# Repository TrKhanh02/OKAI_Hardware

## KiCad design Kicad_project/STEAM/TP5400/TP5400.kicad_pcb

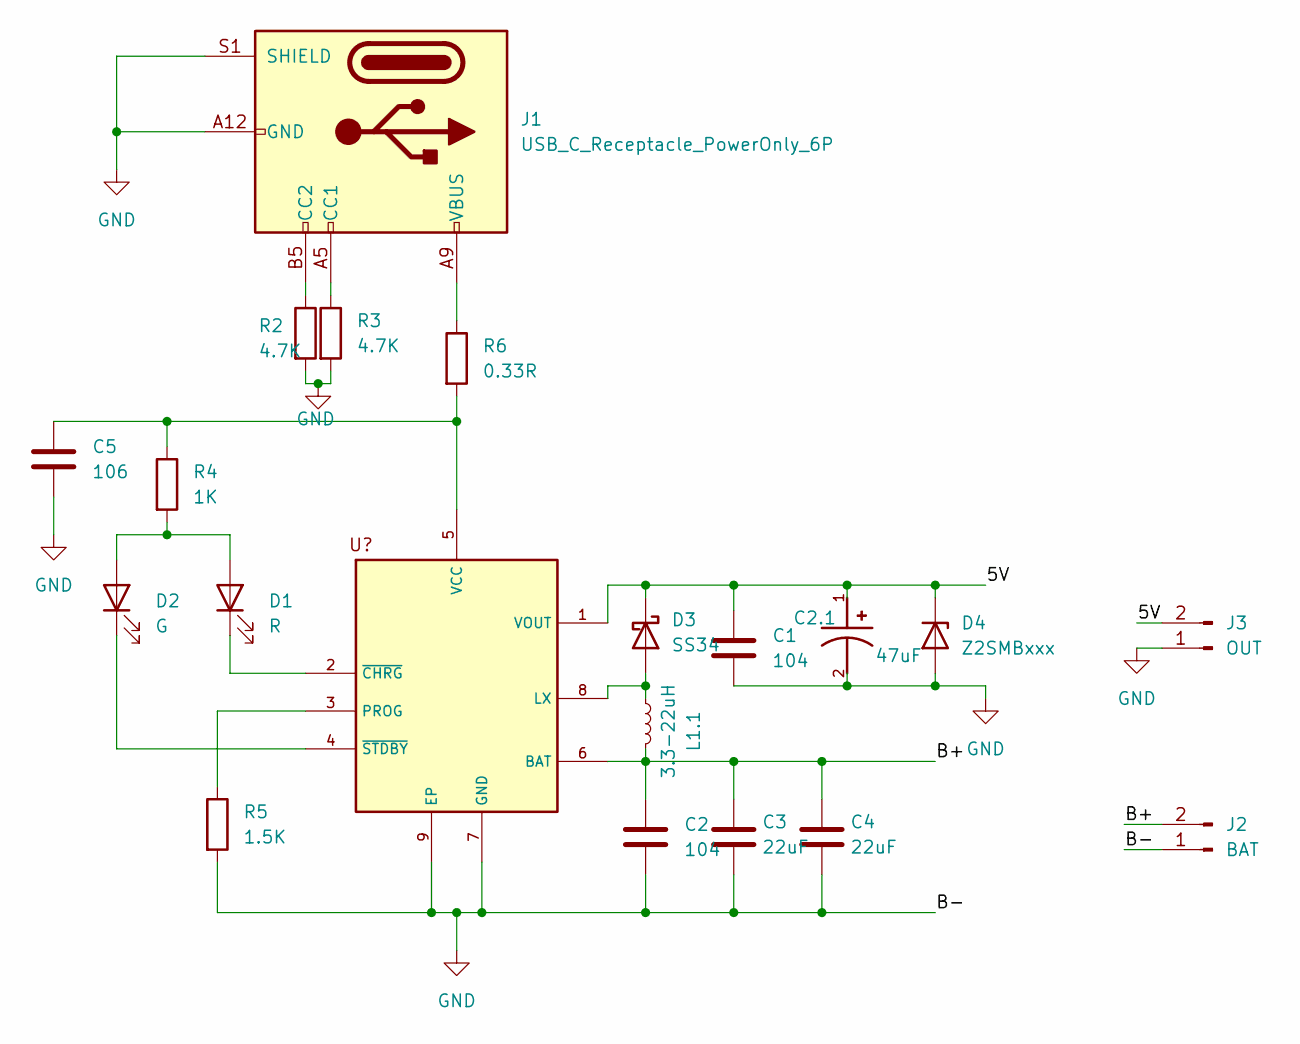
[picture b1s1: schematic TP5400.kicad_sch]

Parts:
C1, C2: 104; C_0805_2012Metric
C2.1: 47uF; CAPMP3216X180N; PARTREV 031320
C3, C4: 22uF; C_1206_3216Metric
C5: 106; C_0805_2012Metric
D1: R; LED_0805_2012Metric
D2: G; LED_0805_2012Metric
D3: SS34; D_SMA
D4: Z2SMBxxx; D_SMB
J1: USB_C_Receptacle_PowerOnly_6P; USB_C_Receptacle_GCT_USB4125-xx-x-0190_6P_TopMnt_Horizontal
J2: BAT; PinSocket_1x02_P2.54mm_Vertical
J3: OUT; PinSocket_1x02_P2.54mm_Vertical
L1.1: 3.3-22uH; L_Ferrocore_DLG-0705
R2, R3: 4.7K; R_0805_2012Metric_Pad1.20x1.40mm_HandSolder
R4: 1K; R_0805_2012Metric_Pad1.20x1.40mm_HandSolder
R5: 1.5K; R_0805_2012Metric_Pad1.20x1.40mm_HandSolder
R6: 0.33R; R_2512_6332Metric
U1: TP5400

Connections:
/5V: C1.1, C2.1.1, D3.1 (K), D4.1 (K), J3.2, U1.1 (VOUT)
/B+: C2.1, C3.1, C4.1, J2.2, L1.1.1, U1.6 (BAT)
GND: C1.2, C2.2, C2.1.2, C3.2, C4.2, C5.2, D4.2 (A), J1.A12 (GND), J1.B12 (GND), J1.S1 (SHIELD), J2.1, J3.1, R2.2, R3.2, R5.2, U1.7 (GND), U1.9 (EP)
unnamed: D1.2 (A), D2.2 (A), R4.2
unnamed: D1.1 (K), U1.2 (~CHRG)
unnamed: D2.1 (K), U1.4 (~STDBY)
unnamed: D3.2 (A), L1.1.2, U1.8 (LX)
unnamed: J1.A5 (CC1), R3.1
unnamed: J1.B5 (CC2), R2.1
unnamed: J1.A9 (VBUS), J1.B9 (VBUS), R6.1
unnamed: R5.1, U1.3 (PROG)
unnamed: C5.1, R4.1, R6.2, U1.5 (VCC)

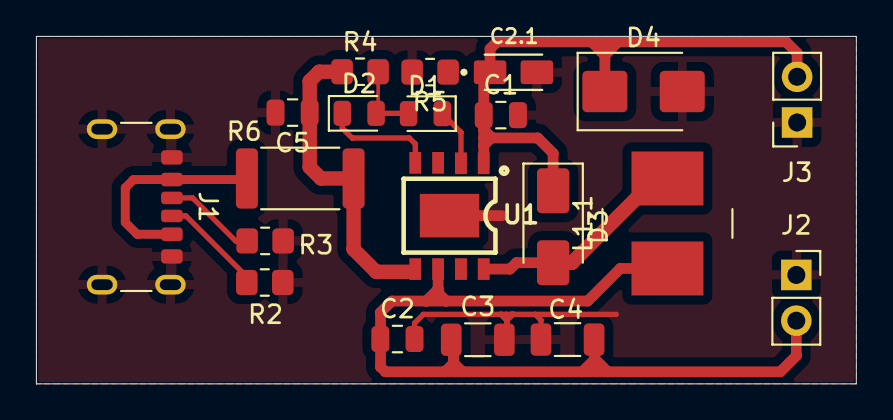
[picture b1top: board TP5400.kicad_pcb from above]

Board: 2 copper layers, 45.5 x 19.3 mm, 20 parts (0 on the bottom side), 12 nets.

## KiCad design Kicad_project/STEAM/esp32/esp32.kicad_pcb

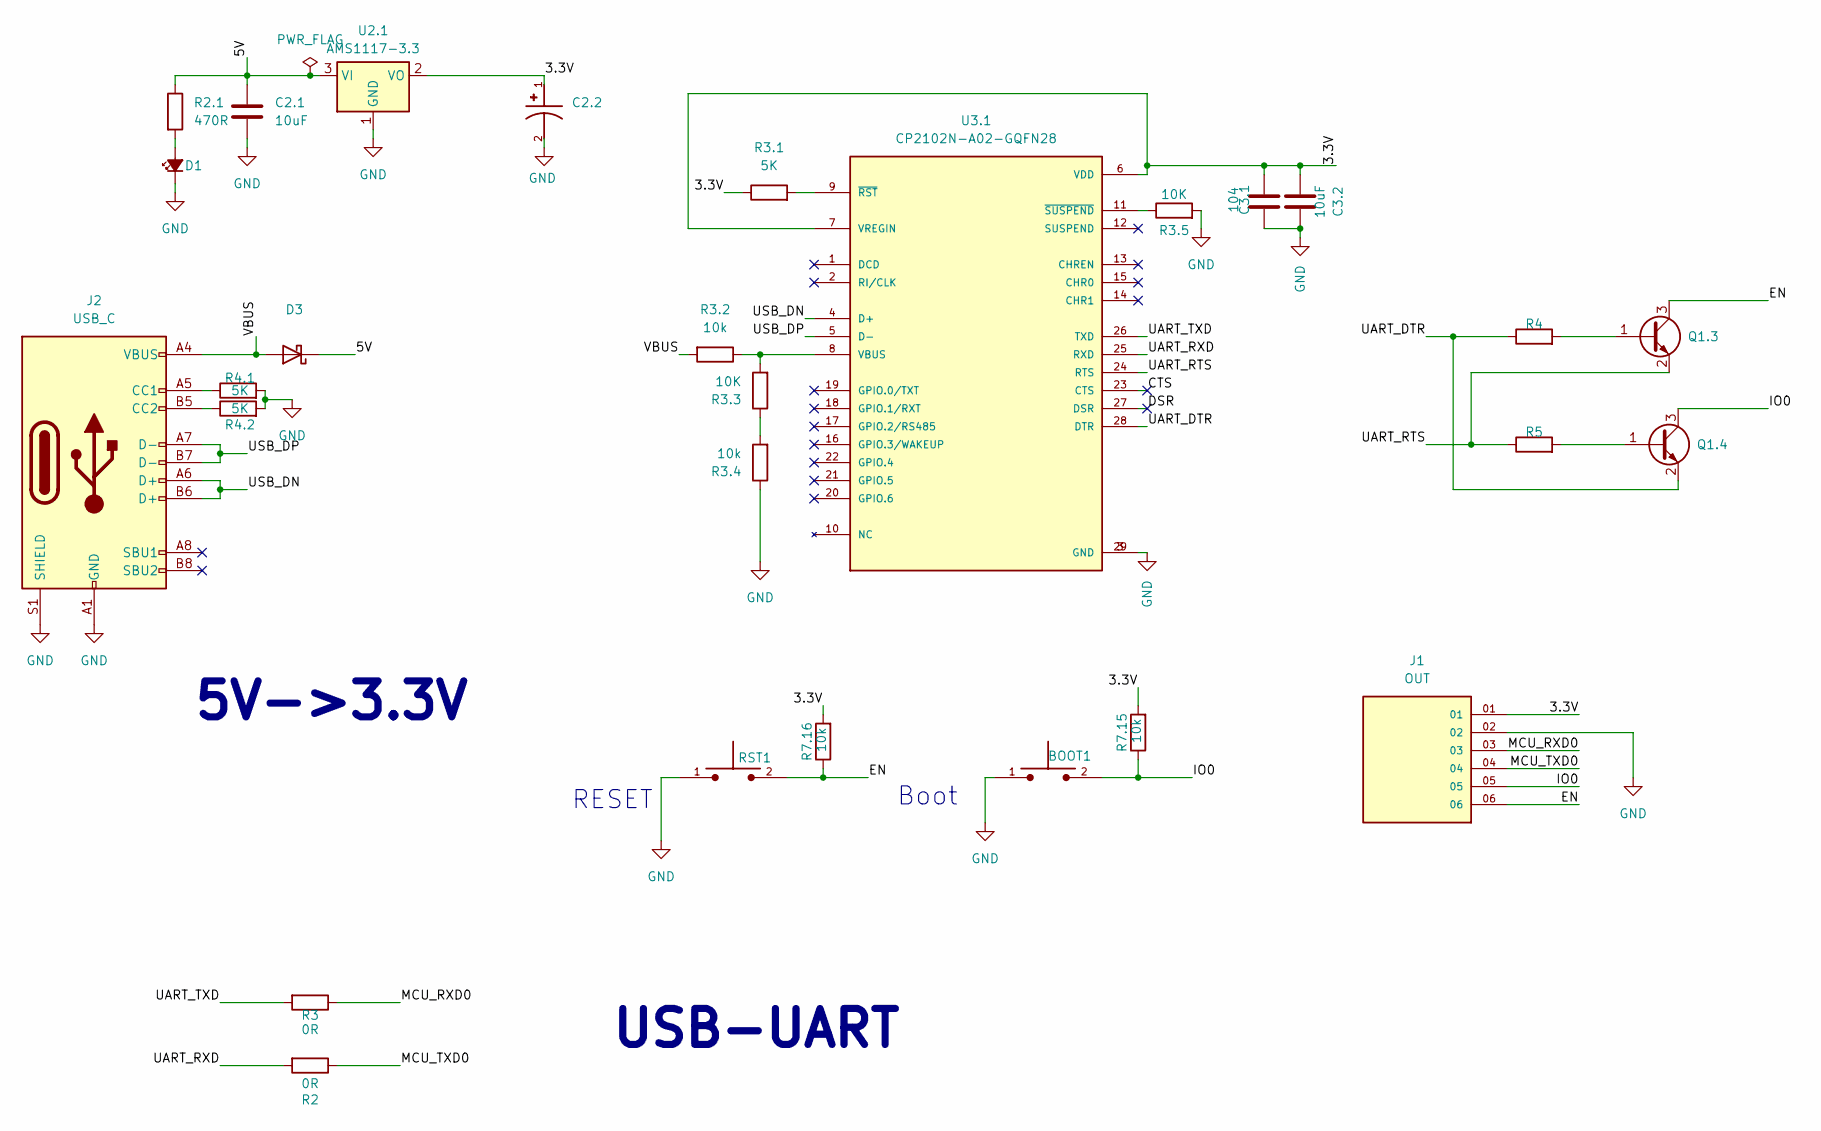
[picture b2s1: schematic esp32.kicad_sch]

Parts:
BOOT1: TS10-63-26-BE-250-SMT-TR; SW_TS10-63-26-BE-250-SMT-TR; PARTREV 1.0
C2.1, C3.2: 10uF; C_0805_2012Metric_Pad1.18x1.45mm_HandSolder
C2.2: 22uF; CAPMP3216X180N; PARTREV 031320
C3.1: 104; C_0805_2012Metric_Pad1.18x1.45mm_HandSolder
D1: LED_Small_Filled; LED_0805_2012Metric_Pad1.15x1.40mm_HandSolder
D3: 1N5819WS; D_SOD-323_HandSoldering
J1: OUT; SAMTEC_TSW-106-08-T-S-LL; PARTREV R
J2: USB_C; USB_C_Receptacle_HRO_TYPE-C-31-M-12
Q1.3, Q1.4: SS8050; SOT-23
R2, R3: 0R; R_0805_2012Metric_Pad1.20x1.40mm_HandSolder
R2.1: 470R; R_0805_2012Metric_Pad1.20x1.40mm_HandSolder
R3.1, R4.1, R4.2: 5K; R_0805_2012Metric_Pad1.20x1.40mm_HandSolder
R3.2, R3.4, R7.15, R7.16: 10k; R_0805_2012Metric_Pad1.20x1.40mm_HandSolder
R3.3, R3.5: 10K; R_0805_2012Metric_Pad1.20x1.40mm_HandSolder
R4, R5: R; R_0805_2012Metric_Pad1.20x1.40mm_HandSolder
RST1: TS10-63-26-BE-250-SMT-TR; SW_TS10-63-26-BE-250-SMT-TR; PARTREV 1.0
U2.1: AMS1117-3.3; SOT-223-3_TabPin2
U3.1: CP2102N-A02-GQFN28; QFN50P500X500X80-29N; PARTREV 1.5

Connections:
/3.3V: C2.2.1, C3.1.2, C3.2.2, J1.01, R3.1.1, R7.15.2, R7.16.2, U2.1.2 (VO), U3.1.6 (VDD), U3.1.7 (VREGIN)
/5V: C2.1.1, D3.1 (K), R2.1.1, U2.1.3 (VI)
/CTS: U3.1.23 (CTS)
/DSR: U3.1.27 (DSR)
/EN: J1.06, Q1.3.3 (C), R7.16.1, RST1.2
/IO0: BOOT1.2, J1.05, Q1.4.3 (C), R7.15.1
/MCU_RXD0: J1.03, R3.1
/MCU_TXD0: J1.04, R2.1
/UART_DTR: Q1.4.2 (E), R4.1, U3.1.28 (DTR)
/UART_RTS: Q1.3.2 (E), R5.1, U3.1.24 (RTS)
/UART_RXD: R2.2, U3.1.25 (RXD)
/UART_TXD: R3.2, U3.1.26 (TXD)
/USB_DN: J2.A6 (D+), J2.B6 (D+), U3.1.4 (D+)
/USB_DP: J2.A7 (D-), J2.B7 (D-), U3.1.5 (D-)
/VBUS: D3.2 (A), J2.A4 (VBUS), J2.A9 (VBUS), J2.B4 (VBUS), J2.B9 (VBUS), R3.2.2
GND: BOOT1.1, C2.1.2, C2.2.2, C3.1.1, C3.2.1, D1.1 (K), J1.02, J2.A1 (GND), J2.A12 (GND), J2.B1 (GND), J2.B12 (GND), J2.S1 (SHIELD), R3.4.1, R3.5.2, R4.1.2, R4.2.2, RST1.1, U2.1.1 (GND), U3.1.3 (GND), U3.1.29 (GND)
unnamed: D1.2 (A), R2.1.2
unnamed: J2.A5 (CC1), R4.1.1
unnamed: J2.B5 (CC2), R4.2.1
unnamed: Q1.3.1 (B), R4.2
unnamed: Q1.4.1 (B), R5.2
unnamed: R3.3.1, R3.4.2
unnamed: R3.2.1, R3.3.2, U3.1.8 (VBUS)
unnamed: R3.1.2, U3.1.9 (~RST)
unnamed: R3.5.1, U3.1.11 (~SUSPEND)

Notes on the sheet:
5V->3.3V
Boot
RESET
USB-UART

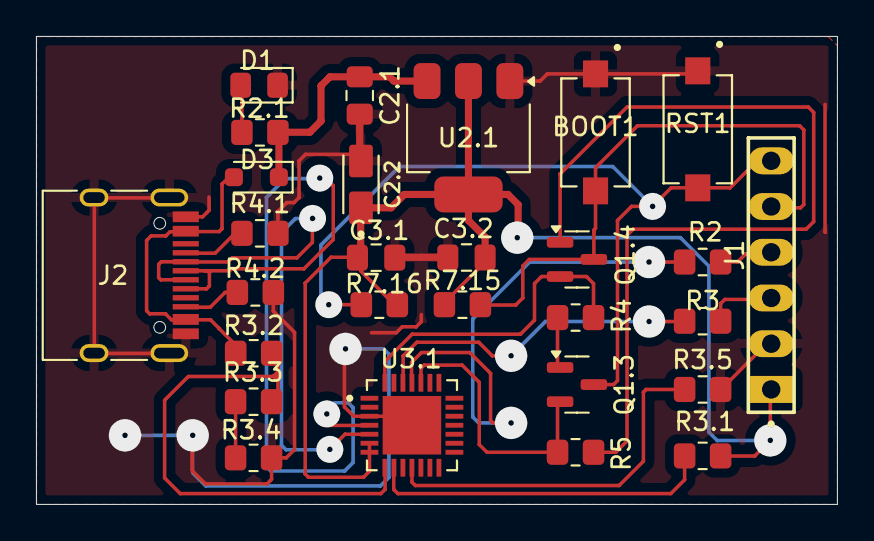
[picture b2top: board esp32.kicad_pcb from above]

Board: 2 copper layers, 44.5 x 26.0 mm, 28 parts (0 on the bottom side), 23 nets.

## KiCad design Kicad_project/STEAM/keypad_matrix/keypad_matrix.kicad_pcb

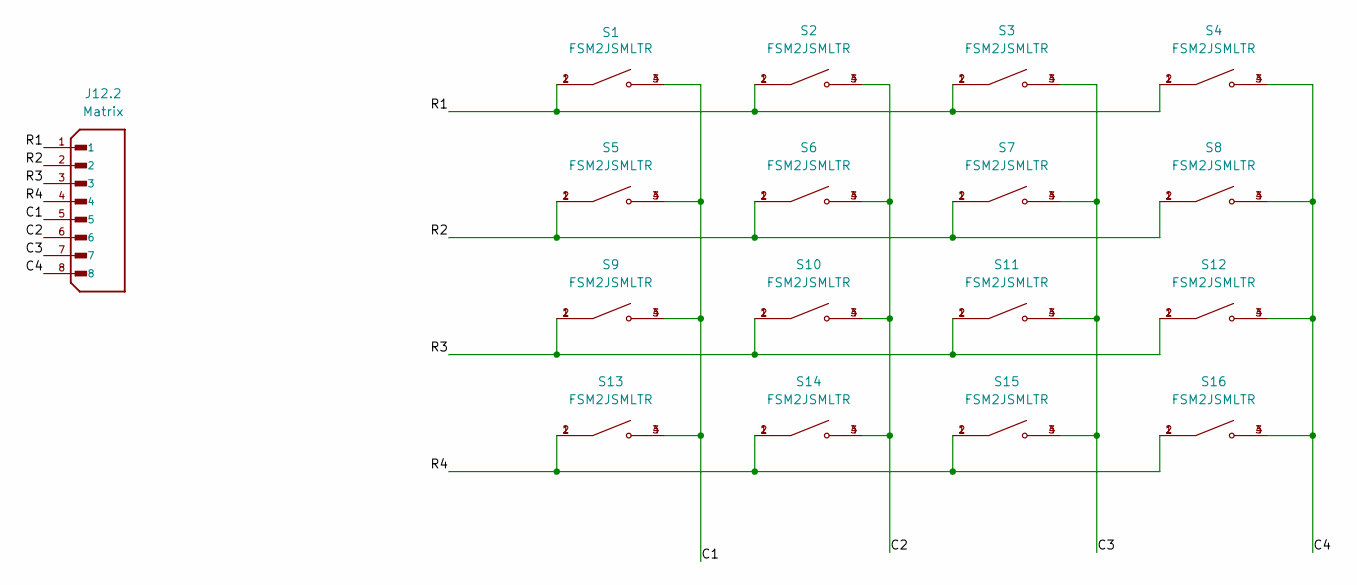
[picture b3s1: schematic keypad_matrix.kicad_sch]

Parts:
J12.2: Matrix; JST_B8B-XH-A_LF__SN_; PARTREV 7/4/21
S1, S2, S3, S4, S5, S6, S7, S8, S9, S10, S11, S12, S13, S14, S15, S16: FSM2JSMLTR; SW_1571527-2; PARTREV V

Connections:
/C1: J12.2.5, S1.3, S1.4, S5.3, S5.4, S9.3, S9.4, S13.3, S13.4
/C2: J12.2.6, S2.3, S2.4, S6.3, S6.4, S10.3, S10.4, S14.3, S14.4
/C3: J12.2.7, S3.3, S3.4, S7.3, S7.4, S11.3, S11.4, S15.3, S15.4
/C4: J12.2.8, S4.3, S4.4, S8.3, S8.4, S12.3, S12.4, S16.3, S16.4
/R1: J12.2.1, S1.1, S1.2, S2.1, S2.2, S3.1, S3.2, S4.1, S4.2
/R2: J12.2.2, S5.1, S5.2, S6.1, S6.2, S7.1, S7.2, S8.1, S8.2
/R3: J12.2.3, S9.1, S9.2, S10.1, S10.2, S11.1, S11.2, S12.1, S12.2
/R4: J12.2.4, S13.1, S13.2, S14.1, S14.2, S15.1, S15.2, S16.1, S16.2

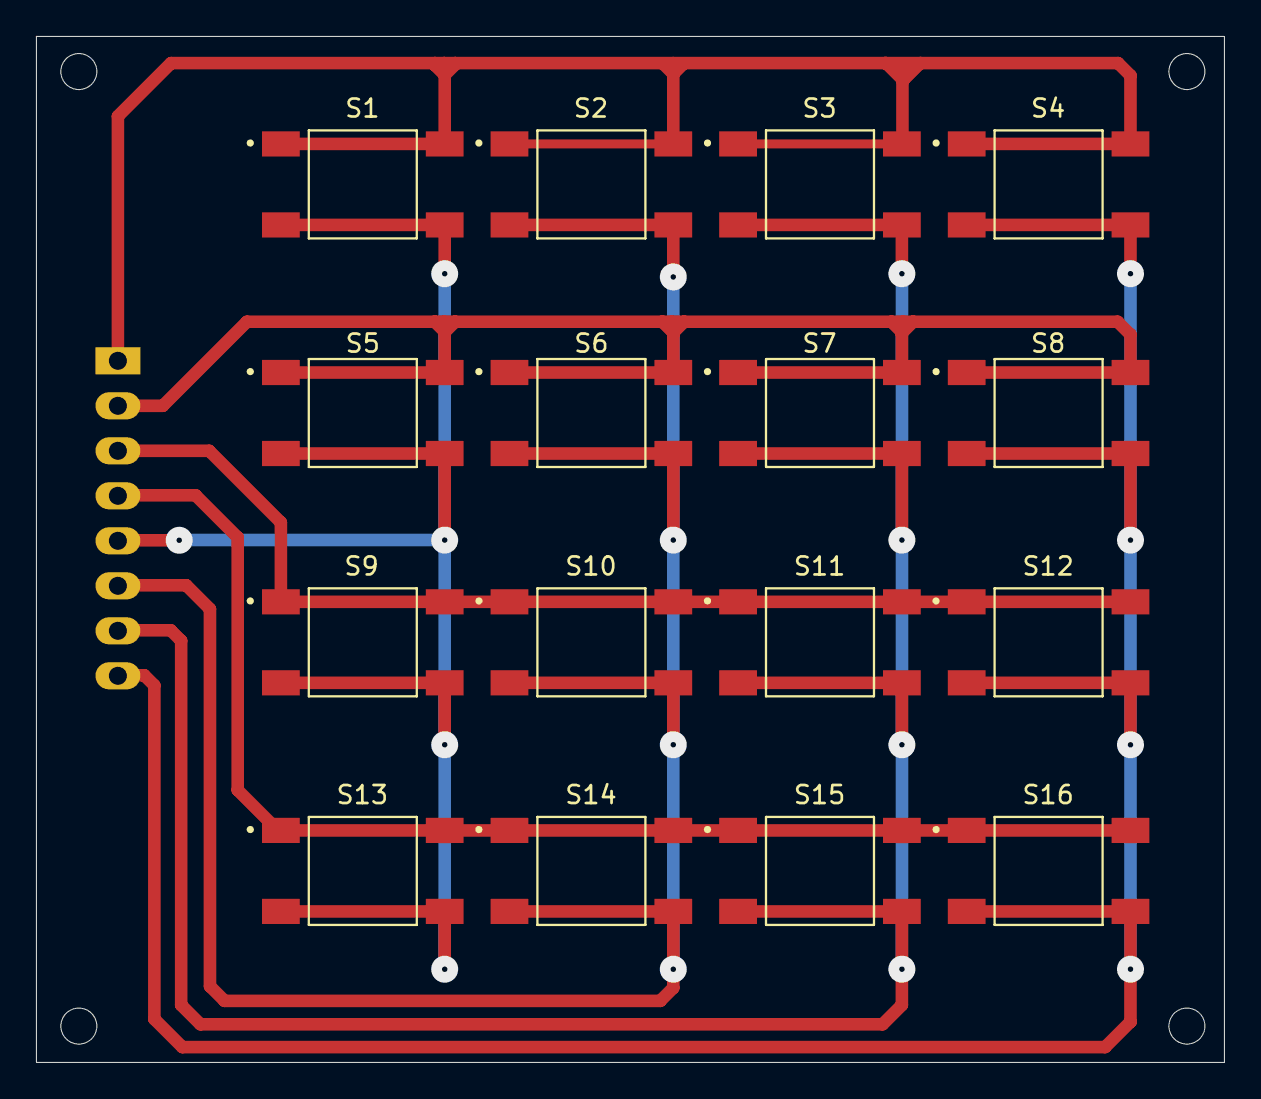
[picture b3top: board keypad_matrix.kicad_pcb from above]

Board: 2 copper layers, 66.0 x 57.0 mm, 17 parts (1 on the bottom side), 8 nets.

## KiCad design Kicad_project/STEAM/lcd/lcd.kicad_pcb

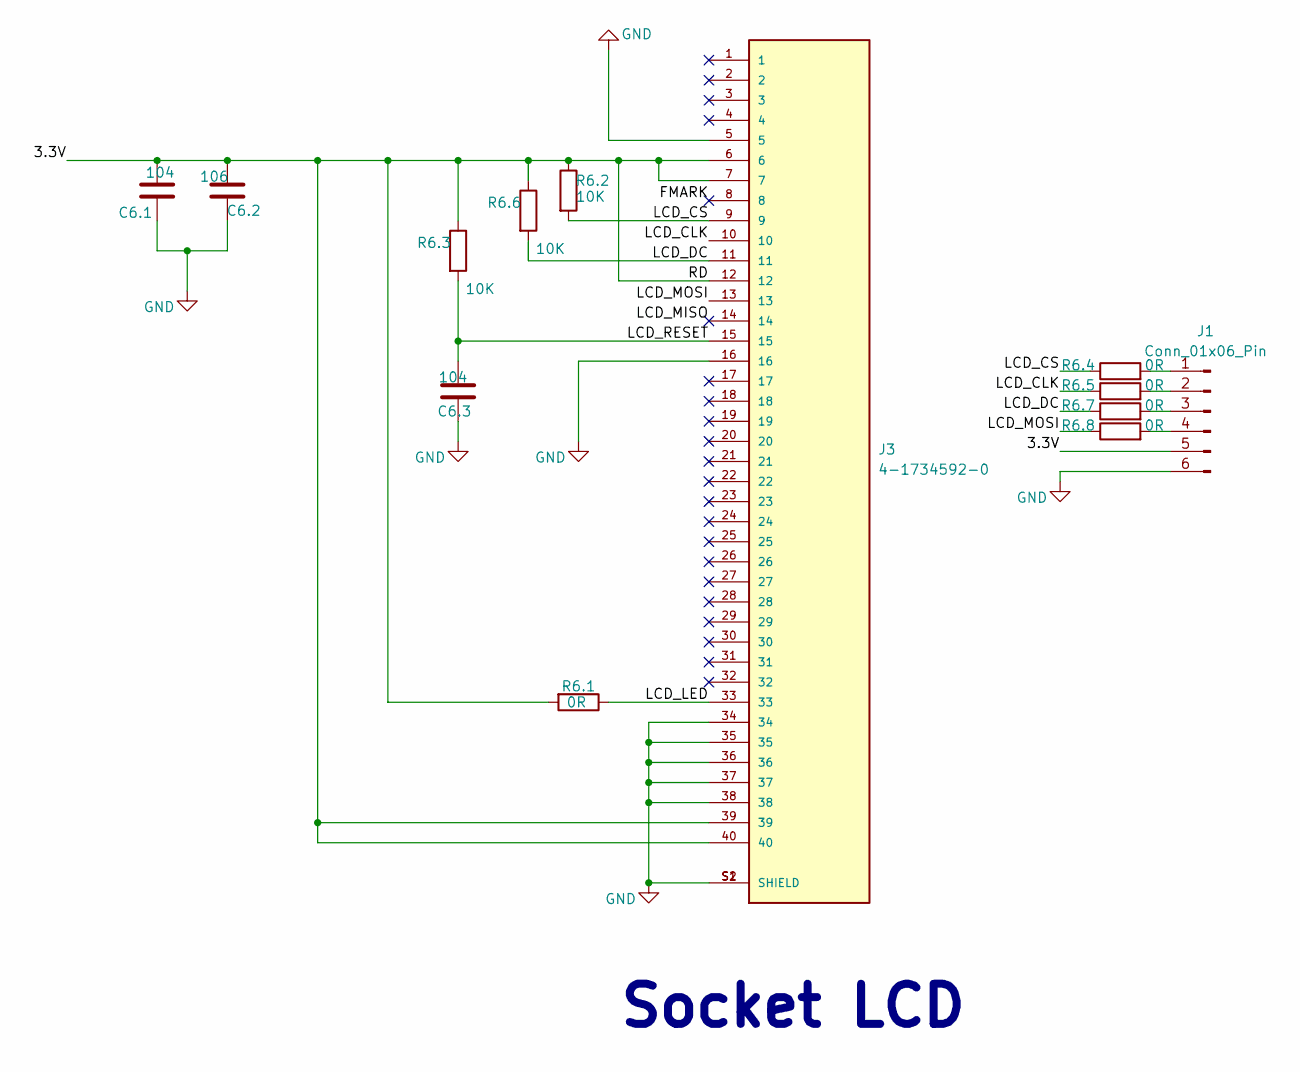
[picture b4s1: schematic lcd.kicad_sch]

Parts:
C6.1, C6.3: 104; C_0805_2012Metric_Pad1.18x1.45mm_HandSolder
C6.2: 106; C_0805_2012Metric_Pad1.18x1.45mm_HandSolder
J1: Conn_01x06_Pin; PinSocket_1x06_P2.54mm_Vertical
J3: 4-1734592-0; TE_4-1734592-0; PARTREV C
R6.1, R6.4, R6.5, R6.7, R6.8: 0R; R_0805_2012Metric_Pad1.20x1.40mm_HandSolder
R6.2, R6.3, R6.6: 10K; R_0805_2012Metric_Pad1.20x1.40mm_HandSolder

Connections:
/3.3V: C6.1.2, C6.2.2, J1.5, J3.6, J3.7, J3.12, J3.39, J3.40, R6.1.2, R6.2.1, R6.3.1, R6.6.1
/FMARK: J3.8
/LCD_CLK: J3.10, R6.5.1
/LCD_CS: J3.9, R6.2.2, R6.4.1
/LCD_DC: J3.11, R6.6.2, R6.7.1
/LCD_LED: J3.33, R6.1.1
/LCD_MISO: J3.14
/LCD_MOSI: J3.13, R6.8.1
/LCD_RESET: C6.3.2, J3.15, R6.3.2
GND: C6.1.1, C6.2.1, C6.3.1, J1.6, J3.5, J3.16, J3.34, J3.35, J3.36, J3.37, J3.38, J3.S1 (SHIELD), J3.S2 (SHIELD)
unnamed: J1.1, R6.4.2
unnamed: J1.2, R6.5.2
unnamed: J1.3, R6.7.2
unnamed: J1.4, R6.8.2

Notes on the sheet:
Socket LCD

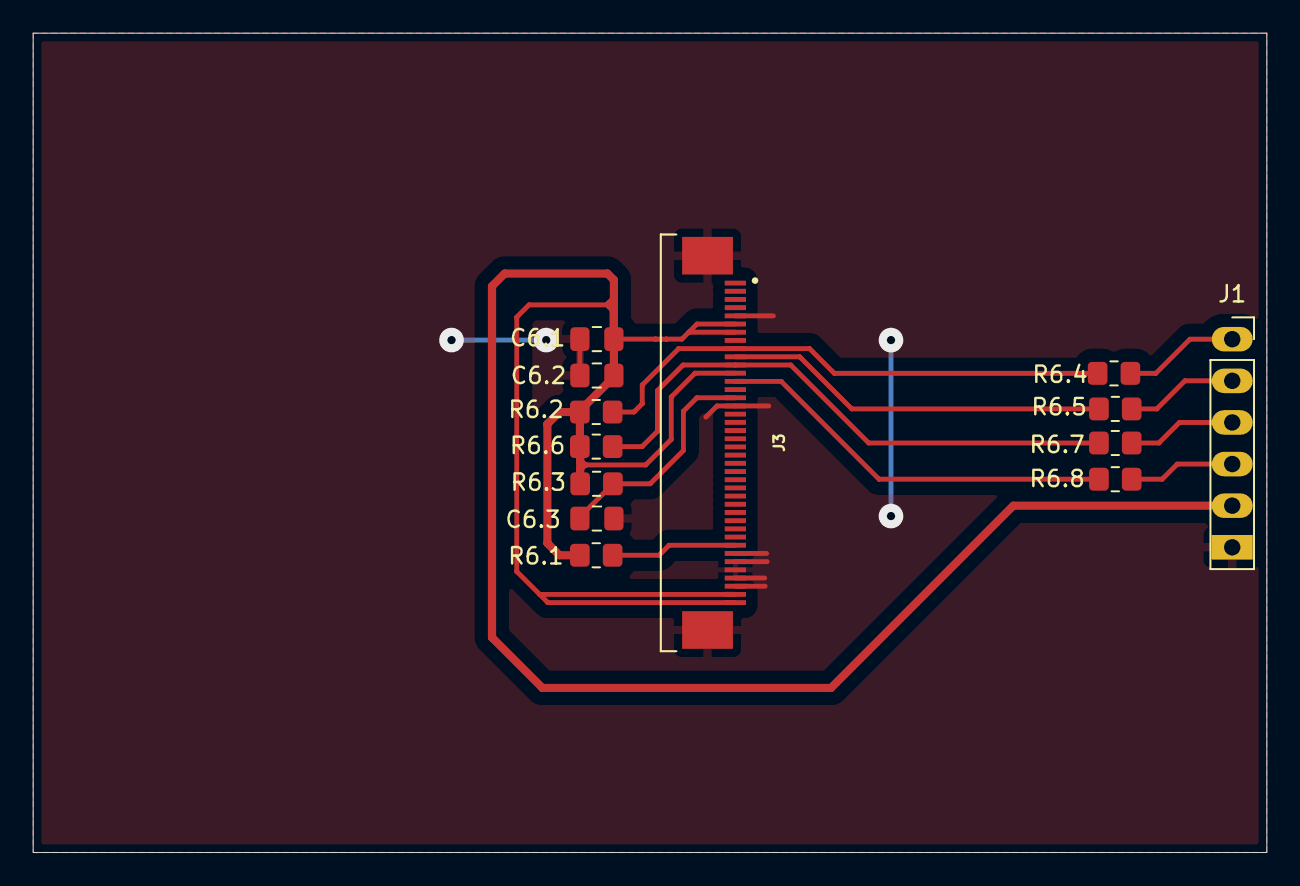
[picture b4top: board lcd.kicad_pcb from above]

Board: 2 copper layers, 75.3 x 50.0 mm, 13 parts (0 on the bottom side), 12 nets.

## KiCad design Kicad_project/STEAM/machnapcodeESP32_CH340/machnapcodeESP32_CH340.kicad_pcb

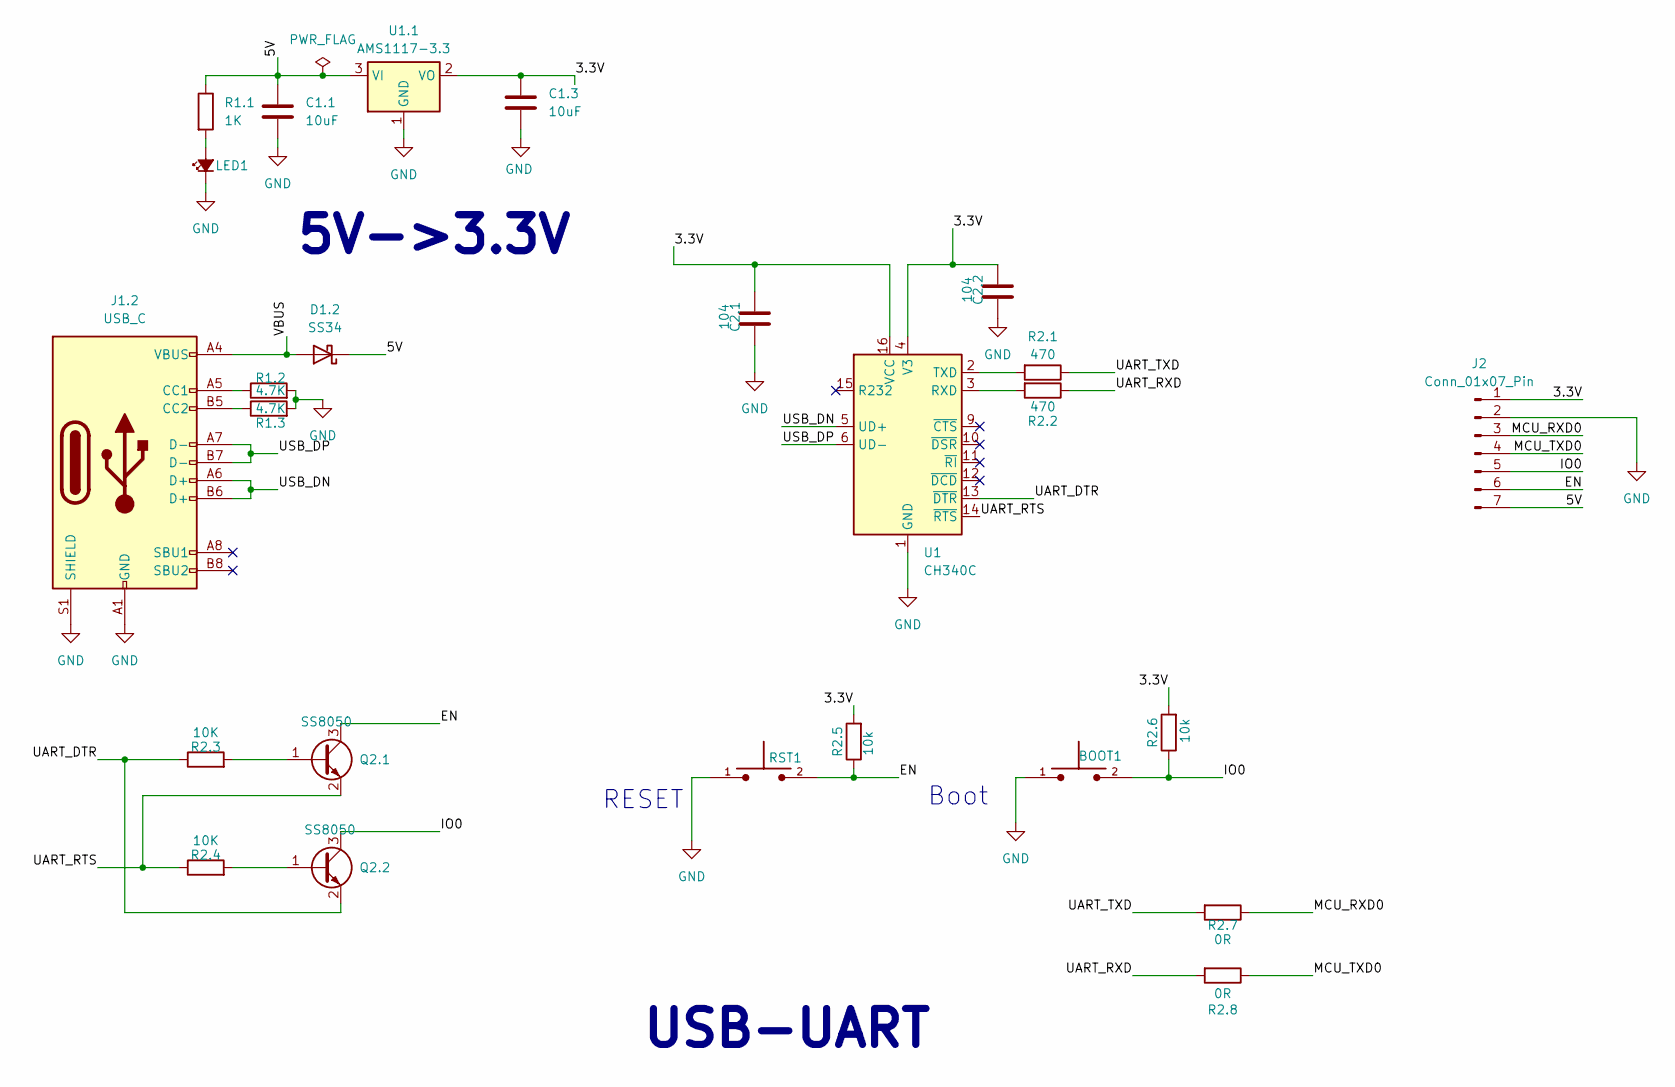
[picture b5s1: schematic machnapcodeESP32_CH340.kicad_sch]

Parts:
BOOT1: TS10-63-26-BE-250-SMT-TR; SW_TS10-63-26-BE-250-SMT-TR; PARTREV 1.0
C1.1, C1.3: 10uF; C_0805_2012Metric_Pad1.18x1.45mm_HandSolder
C2.1, C2.2: 104; C_0805_2012Metric_Pad1.18x1.45mm_HandSolder
D1.2: SS34; D_SMA
J1.2: USB_C; USB_C_Receptacle_HRO_TYPE-C-31-M-12
J2: Conn_01x07_Pin; PinSocket_1x07_P2.54mm_Vertical
LED1: LED_Small_Filled; LED_0805_2012Metric_Pad1.15x1.40mm_HandSolder
Q2.1, Q2.2: SS8050; SOT-23
R1.1: 1K; R_0805_2012Metric_Pad1.20x1.40mm_HandSolder
R1.2, R1.3: 4.7K; R_0805_2012Metric_Pad1.20x1.40mm_HandSolder
R2.1, R2.2: 470; R_0805_2012Metric_Pad1.20x1.40mm_HandSolder
R2.3, R2.4: 10K; R_0805_2012Metric_Pad1.20x1.40mm_HandSolder
R2.5, R2.6: 10k; R_0805_2012Metric_Pad1.20x1.40mm_HandSolder
R2.7, R2.8: 0R; R_0805_2012Metric_Pad1.20x1.40mm_HandSolder
RST1: TS10-63-26-BE-250-SMT-TR; SW_TS10-63-26-BE-250-SMT-TR; PARTREV 1.0
U1: CH340C; SOIC-16_3.9x9.9mm_P1.27mm
U1.1: AMS1117-3.3; SOT-223-3_TabPin2

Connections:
/3.3V: C1.3.1, C2.1.2, C2.2.2, J2.1, R2.5.2, R2.6.2, U1.4 (V3), U1.16 (VCC), U1.1.2 (VO)
/5V: C1.1.1, D1.2.1 (K), J2.7, R1.1.1, U1.1.3 (VI)
/EN: J2.6, Q2.1.3 (C), R2.5.1, RST1.2
/IO0: BOOT1.2, J2.5, Q2.2.3 (C), R2.6.1
/MCU_RXD0: J2.3, R2.7.1
/MCU_TXD0: J2.4, R2.8.1
/UART_DTR: Q2.2.2 (E), R2.3.1, U1.13 (~DTR)
/UART_RTS: Q2.1.2 (E), R2.4.1, U1.14 (~RTS)
/UART_RXD: R2.2.1, R2.8.2
/UART_TXD: R2.1.1, R2.7.2
/USB_DN: J1.2.A6 (D+), J1.2.B6 (D+), U1.5 (UD+)
/USB_DP: J1.2.A7 (D-), J1.2.B7 (D-), U1.6 (UD-)
/VBUS: D1.2.2 (A), J1.2.A4 (VBUS), J1.2.A9 (VBUS), J1.2.B4 (VBUS), J1.2.B9 (VBUS)
GND: BOOT1.1, C1.1.2, C1.3.2, C2.1.1, C2.2.1, J1.2.A1 (GND), J1.2.A12 (GND), J1.2.B1 (GND), J1.2.B12 (GND), J1.2.S1 (SHIELD), J2.2, LED1.1 (K), R1.2.2, R1.3.2, RST1.1, U1.1 (GND), U1.1.1 (GND)
unnamed: J1.2.A5 (CC1), R1.2.1
unnamed: J1.2.B5 (CC2), R1.3.1
unnamed: LED1.2 (A), R1.1.2
unnamed: Q2.1.1 (B), R2.3.2
unnamed: Q2.2.1 (B), R2.4.2
unnamed: R2.2.2, U1.3 (RXD)
unnamed: R2.1.2, U1.2 (TXD)

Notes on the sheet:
Boot
5V->3.3V
USB-UART
RESET

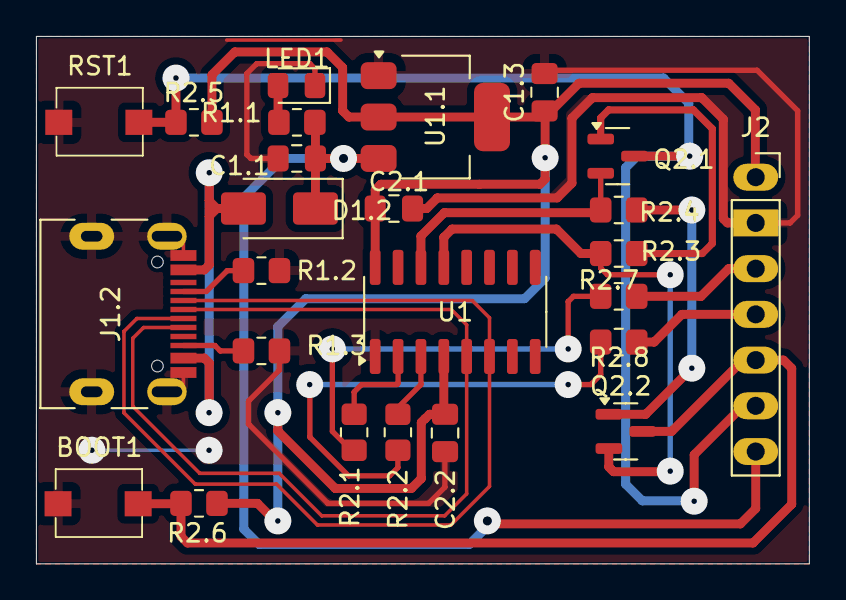
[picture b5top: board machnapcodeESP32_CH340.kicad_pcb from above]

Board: 2 copper layers, 42.9 x 29.3 mm, 25 parts (0 on the bottom side), 21 nets.

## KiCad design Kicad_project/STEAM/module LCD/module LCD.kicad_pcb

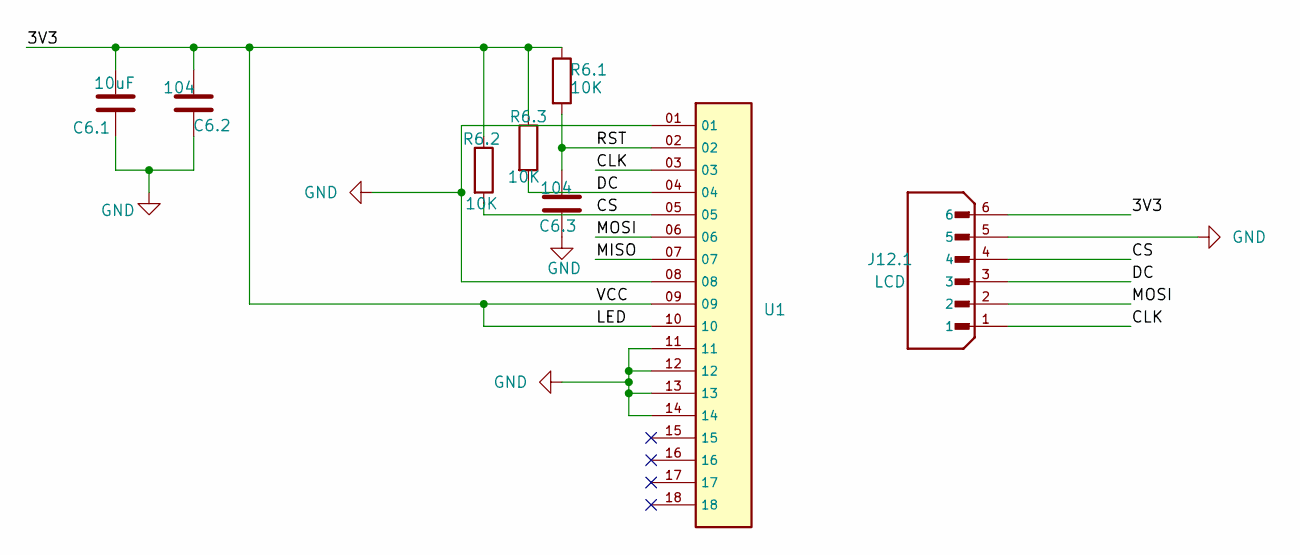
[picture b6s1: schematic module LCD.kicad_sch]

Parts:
C6.1: 10uF; C_0805_2012Metric_Pad1.18x1.45mm_HandSolder
C6.2, C6.3: 104; C_0805_2012Metric_Pad1.18x1.45mm_HandSolder
J12.1: LCD; JST_B6B-XH-A_LF__SN_; PARTREV 7/4/21
R6.1, R6.2, R6.3: 10K; R_0805_2012Metric_Pad1.20x1.40mm_HandSolder
U1: Pad_18P_0.8

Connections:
/3V3: C6.1.2, C6.2.2, J12.1.6, R6.1.1, R6.2.1, R6.3.1, U1.09, U1.10
/CLK: J12.1.1, U1.03
/CS: J12.1.4, R6.2.2, U1.05
/DC: J12.1.3, R6.3.2, U1.04
/MISO: U1.07
/MOSI: J12.1.2, U1.06
/RST: C6.3.2, R6.1.2, U1.02
GND: C6.1.1, C6.2.1, C6.3.1, J12.1.5, U1.01, U1.08, U1.11, U1.12, U1.13, U1.14

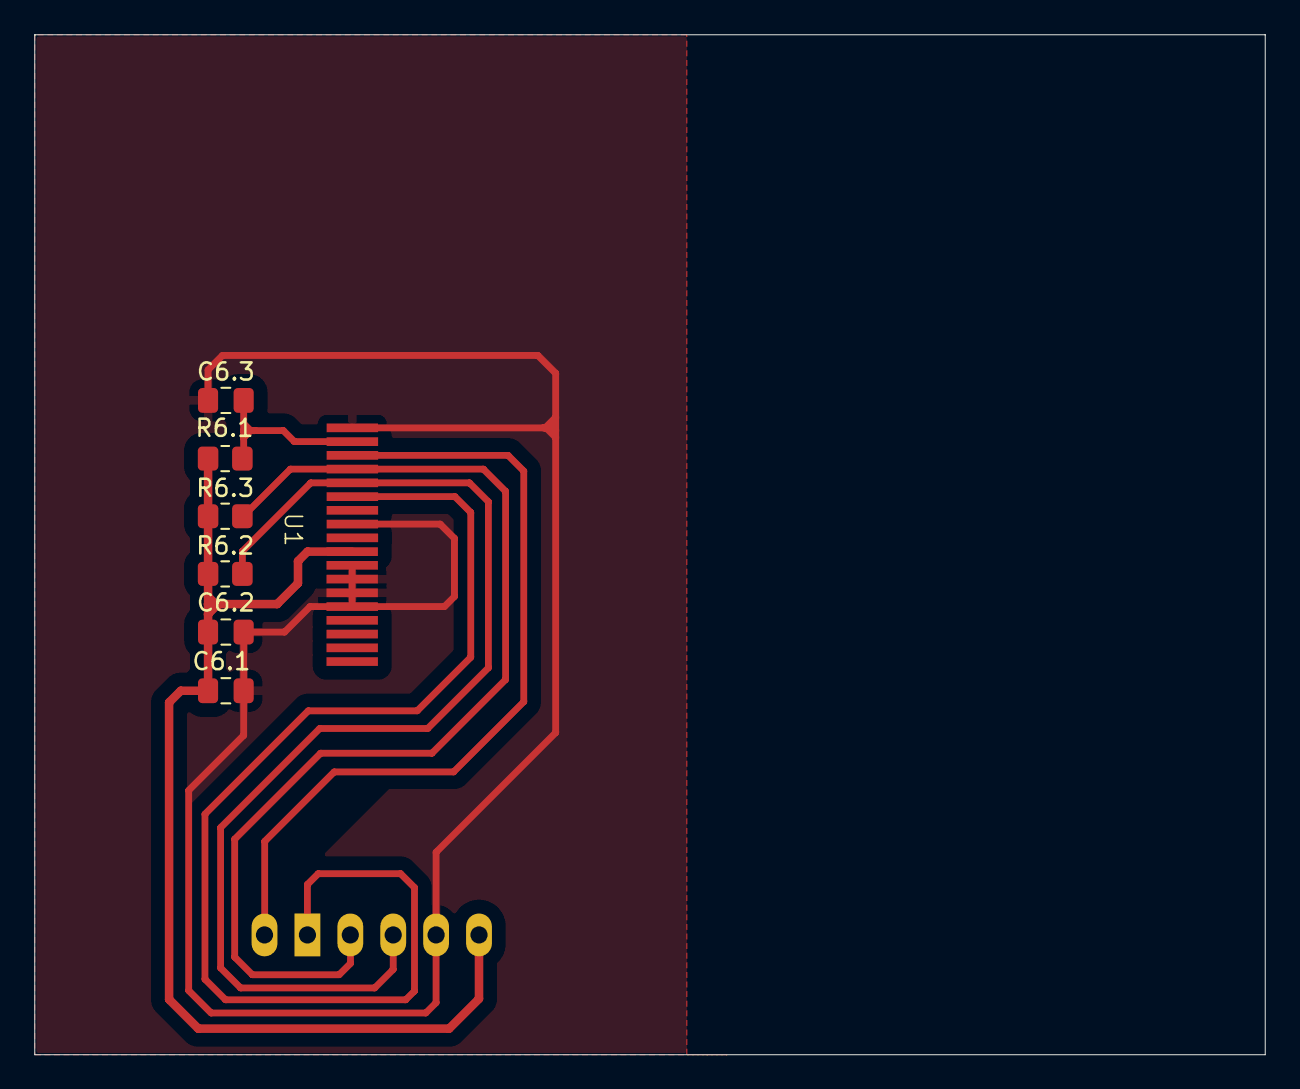
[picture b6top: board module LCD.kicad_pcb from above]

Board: 2 copper layers, 71.7 x 59.4 mm, 8 parts (1 on the bottom side), 7 nets.
